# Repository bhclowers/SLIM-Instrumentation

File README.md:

# SLIM-Instrumentation
Design repository for SLIM boards and vacuum enclosures in the Clowers' Lab at WSU. Solidworks is the primary design tool for mechanical elements. For those without access to this tool, [OnShape](https://www.onshape.com/en/) is a highly capable tool that can import Solidworks assemblies and parts.  

SLIM Chamber Example:
<center></center>

* These research products were developed with the support of the [NIGMS](https://www.nigms.nih.gov/) R01-GM140129

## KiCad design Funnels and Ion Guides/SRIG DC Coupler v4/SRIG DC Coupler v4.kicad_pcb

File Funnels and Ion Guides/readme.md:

## Ion Funnel and SRIGs
#
Design repository for the Ion Funnels and Stacked Ring Ion Guides (SRIG) used to introduce ions into the SLIM systems at WSU. These boards are designed in KiCad with the layout designed to be modular. This ion guide environment can be extended to accommodate different ion guide diameters and even used to create ion funnels. A SRIG/Funnel Layout tool can be found here: [KiCad Layout Script](https://github.com/bhclowers/Instrument-Design/tree/master/KiCad%20Scripts) 

SRIG Ion Funnel Example:
<center></center>

* These research products were developed with the support of the [NIGMS](https://www.nigms.nih.gov/) R01-GM140129

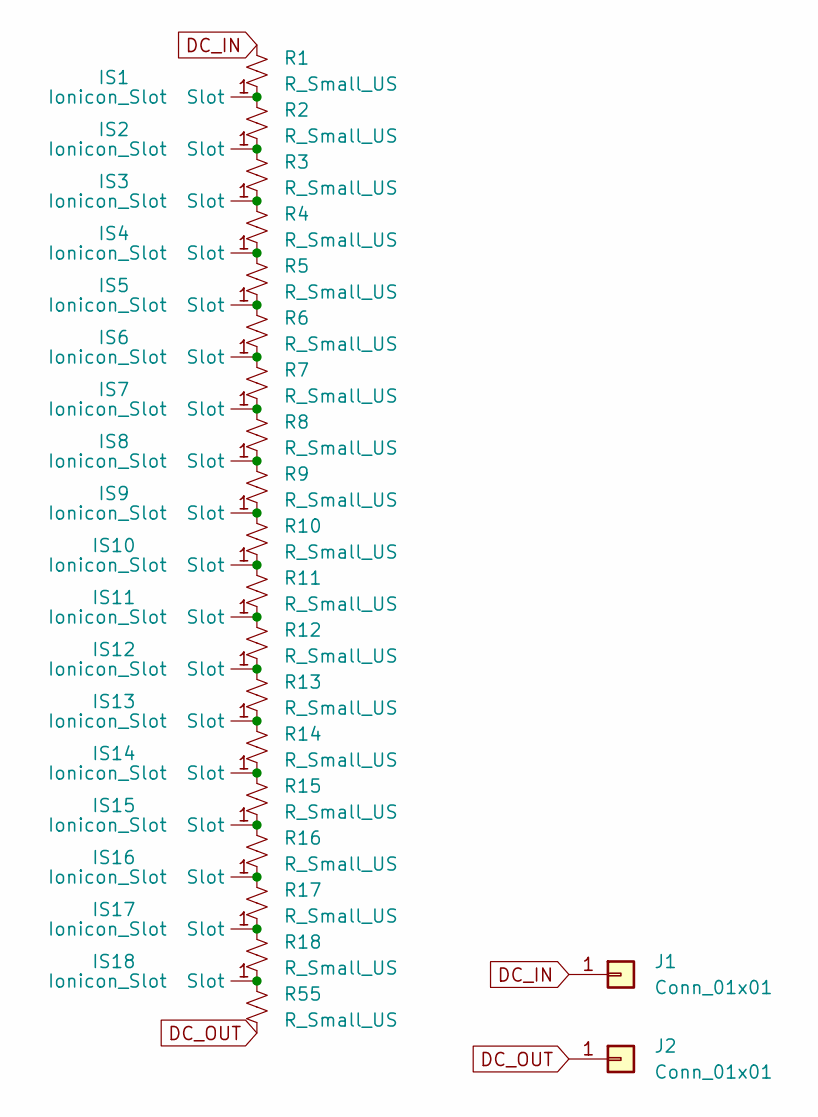
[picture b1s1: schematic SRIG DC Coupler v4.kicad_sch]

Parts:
IS1, IS2, IS3, IS4, IS5, IS6, IS7, IS8, IS9, IS10, IS11, IS12, IS13, IS14, IS15, IS16, IS17, IS18: Ionicon_Slot; IGSlot
J1, J2: Conn_01x01; PinHeader_1x01_P2.54mm_Vertical
R1, R2, R3, R4, R5, R6, R7, R8, R9, R10, R11, R12, R13, R14, R15, R16, R17, R18, R55: R_Small_US; R_1206_3216Metric

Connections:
DC_IN: J1.1, R1.1
DC_OUT: J2.1, R55.2
unnamed: IS1.1 (Slot), R1.2, R2.1
unnamed: IS2.1 (Slot), R2.2, R3.1
unnamed: IS3.1 (Slot), R3.2, R4.1
unnamed: IS4.1 (Slot), R4.2, R5.1
unnamed: IS5.1 (Slot), R5.2, R6.1
unnamed: IS6.1 (Slot), R6.2, R7.1
unnamed: IS7.1 (Slot), R7.2, R8.1
unnamed: IS8.1 (Slot), R8.2, R9.1
unnamed: IS9.1 (Slot), R9.2, R10.1
unnamed: IS10.1 (Slot), R10.2, R11.1
unnamed: IS11.1 (Slot), R11.2, R12.1
unnamed: IS12.1 (Slot), R12.2, R13.1
unnamed: IS13.1 (Slot), R13.2, R14.1
unnamed: IS14.1 (Slot), R14.2, R15.1
unnamed: IS15.1 (Slot), R15.2, R16.1
unnamed: IS16.1 (Slot), R16.2, R17.1
unnamed: IS17.1 (Slot), R17.2, R18.1
unnamed: IS18.1 (Slot), R18.2, R55.1

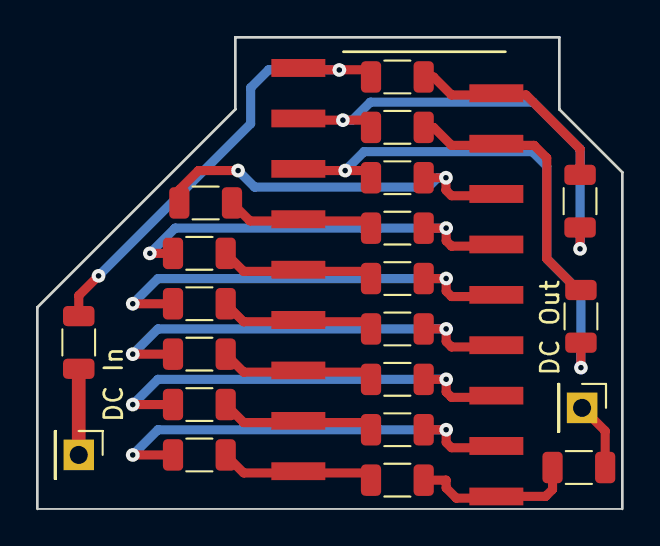
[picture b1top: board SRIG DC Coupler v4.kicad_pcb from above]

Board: 2 copper layers, 32.5 x 26.2 mm, 39 parts (0 on the bottom side), 20 nets.

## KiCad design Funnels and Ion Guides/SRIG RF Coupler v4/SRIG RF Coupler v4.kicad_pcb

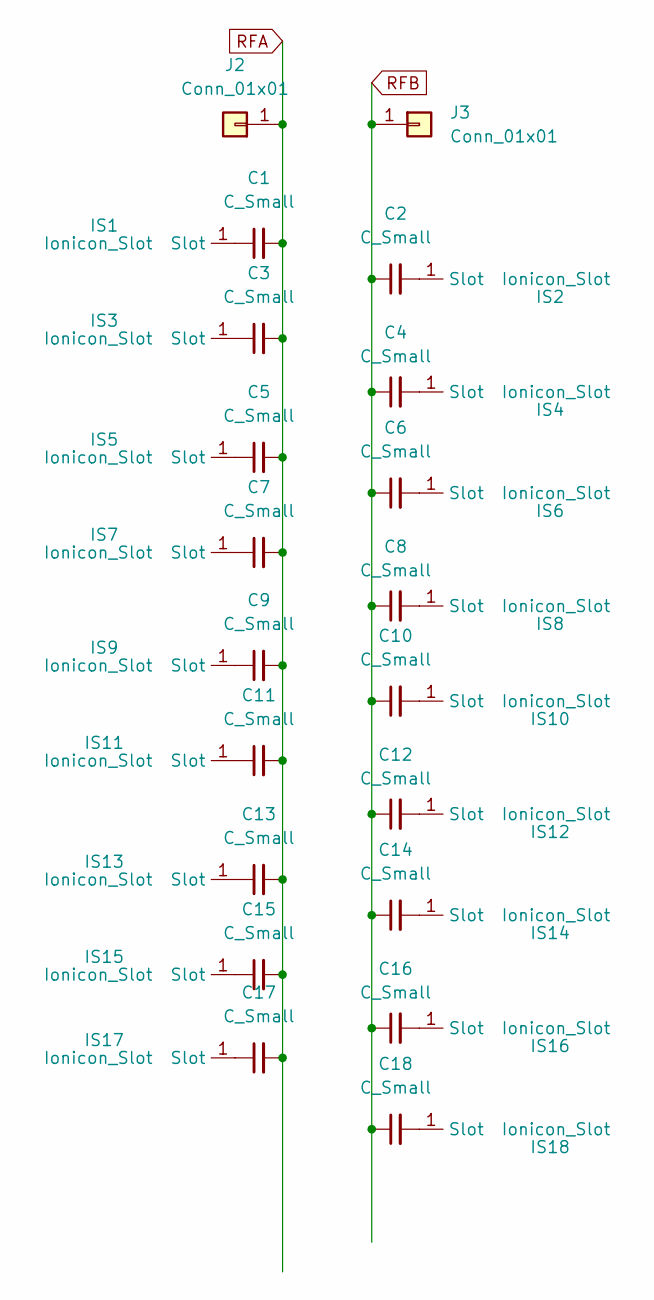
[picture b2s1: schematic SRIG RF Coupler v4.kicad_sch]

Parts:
C1, C2, C3, C4, C5, C6, C7, C8, C9, C10, C11, C12, C13, C14, C15, C16, C17, C18: C_Small; C_1206_3216Metric
IS1, IS2, IS3, IS4, IS5, IS6, IS7, IS8, IS9, IS10, IS11, IS12, IS13, IS14, IS15, IS16, IS17, IS18: Ionicon_Slot; IGSlot
J2, J3: Conn_01x01; PinHeader_1x01_P2.54mm_Vertical

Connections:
unnamed: C1.1, IS1.1 (Slot)
unnamed: C2.2, IS2.1 (Slot)
unnamed: C3.1, IS3.1 (Slot)
unnamed: C4.2, IS4.1 (Slot)
unnamed: C5.1, IS5.1 (Slot)
unnamed: C6.2, IS6.1 (Slot)
unnamed: C7.1, IS7.1 (Slot)
unnamed: C8.2, IS8.1 (Slot)
unnamed: C9.1, IS9.1 (Slot)
unnamed: C10.2, IS10.1 (Slot)
unnamed: C11.1, IS11.1 (Slot)
unnamed: C12.2, IS12.1 (Slot)
unnamed: C13.1, IS13.1 (Slot)
unnamed: C14.2, IS14.1 (Slot)
unnamed: C15.1, IS15.1 (Slot)
unnamed: C16.2, IS16.1 (Slot)
unnamed: C17.1, IS17.1 (Slot)
unnamed: C18.2, IS18.1 (Slot)
RFA: C1.2, C3.2, C5.2, C7.2, C9.2, C11.2, C13.2, C15.2, C17.2, J2.1
RFB: C2.1, C4.1, C6.1, C8.1, C10.1, C12.1, C14.1, C16.1, C18.1, J3.1

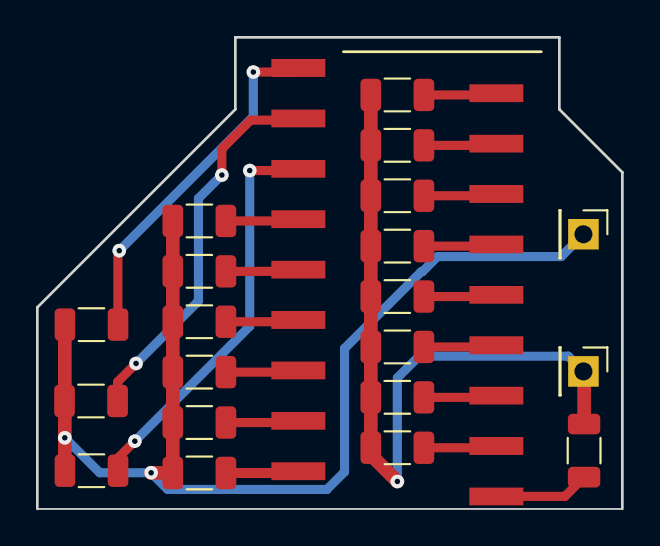
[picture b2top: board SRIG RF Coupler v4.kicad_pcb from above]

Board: 2 copper layers, 32.5 x 26.2 mm, 38 parts (0 on the bottom side), 20 nets.

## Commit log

2023-05-01 Added Faraday plate

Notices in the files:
Funnels and Ion Guides/readme.md:
License: LGPL v3
